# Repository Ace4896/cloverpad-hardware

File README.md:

# Cloverpad - Hardware

**NOTE**: This project is still a work-in-progress, this note will be removed once it's ready!

This repository contains the hardware designs for the Cloverpad, a 3-key keypad for osu! themed after [MORE MORE JUMP!](https://www.sekaipedia.org/wiki/MORE_MORE_JUMP!) from Project Sekai.

... picture of finished keypad ...

There are two PCB variants for this keypad:

- **Cloverpad HE**: PCB for use with hall effect switches (e.g. Wooting Lekker, Gateron KS-20), themed after [Haruka Kiritani](https://www.sekaipedia.org/wiki/Kiritani_Haruka).
- **Cloverpad MX**: PCB for use with regular MX-style mechanical switches, themed after [Minori Hanasato](https://www.sekaipedia.org/wiki/Hanasato_Minori).

## Usage

Make sure you have the following things installed:

- [FreeCAD 0.21](https://www.freecad.org/)
- [KiCad 8](https://www.kicad.org/) with the following plugins:
  - [marbastlib Keyboard Footprints](https://github.com/ebastler/marbastlib)
  - [KiCad JLCPCB Tools](https://github.com/Bouni/kicad-jlcpcb-tools) (if you're using JLC for manufacturing the PCB)

Clone the repository:

```bash
git clone git@github.com:Cloverpad/cloverpad-hardware.git
```

Then navigate to the folder for the revision you're interested in:

- [Rev. 2](./rev2)
- [Rev. 1](./rev1) (Cloverpad MX only; not recommended due to design flaws)

## Additional Files

These project files were used to help design the case and PCB:

- [**assets**](./assets): Miscellaneous assets - logos, character emotes etc.
- [**notes**](./notes): Personal notes for this project - you may find them useful if you're designing a keypad/keyboard of your own
- [**kle**](./kle): Keypad layouts generated by [Keyboard Layout Editor](http://www.keyboard-layout-editor.com/)

## Licensing

This project is licensed under [CERN-OHL-S-2.0](./LICENSE).

Below is a list of assets used from other projects:

- [Project Sekai: Colourful Stage!](https://www.colorfulstage.com/)
  - © SEGA / © Colorful Palette Inc. / © Crypton Future Media, INC.
  - This is a fan project and has no affiliation with SEGA, Colorful Palette, or Crypton Future Media.
  - Assets from MORE MORE JUMP! and its characters are used in the PCB designs.
- [ConstantinoSchillebeeckx/cherry-mx-switch](https://github.com/ConstantinoSchillebeeckx/cherry-mx-switch)
  - [MIT License](https://github.com/ConstantinoSchillebeeckx/cherry-mx-switch/blob/master/LICENSE)
  - The Cherry MX Switch 3D model is used in the minimal PCB.
- [ebastler/marbastlib](https://github.com/ebastler/marbastlib)
  - [CERN-OHL-P-2.0 License](https://github.com/ebastler/marbastlib/blob/main/LICENSE)
  - Various KiCad symbols and footprints are used in the PCB designs and the minimal PCB.

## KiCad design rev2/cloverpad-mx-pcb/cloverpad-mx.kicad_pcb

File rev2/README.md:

# Cloverpad rev. 2

**NOTE**: This revision is still a work-in-progress, this note will be removed once it's ready!

This folder contains the hardware designs for the Cloverpad rev. 2. This is an incremental improvement over rev. 1, which resolves various issues with the 3D printed case.

Features:

- RP2040 MCU
- Cloverpad HE supports hot-swappable MX-style hall effect switches
- Cloverpad MX supports hot-swappable MX-style digital switches
- 3D printed case w/ threaded inserts

Required parts (for reference):

- 3D printed case + PCB
- USB Type-C cable
- 8x M2x6mm screws
- 8x M2x3mm threaded inserts
- Rubber feet

## Design Files

- [`cloverpad-case.FCStd`](./cloverpad-case.FCStd): FreeCAD 0.21 project for the 3D printed case.
- [`cloverpad-he-pcb`](./cloverpad-he-pcb): KiCad 8 project for the Cloverpad HE rev. 2 PCB.
- [`cloverpad-mx-pcb`](./cloverpad-mx-pcb): KiCad 8 project for the Cloverpad MX rev. 2 PCB.

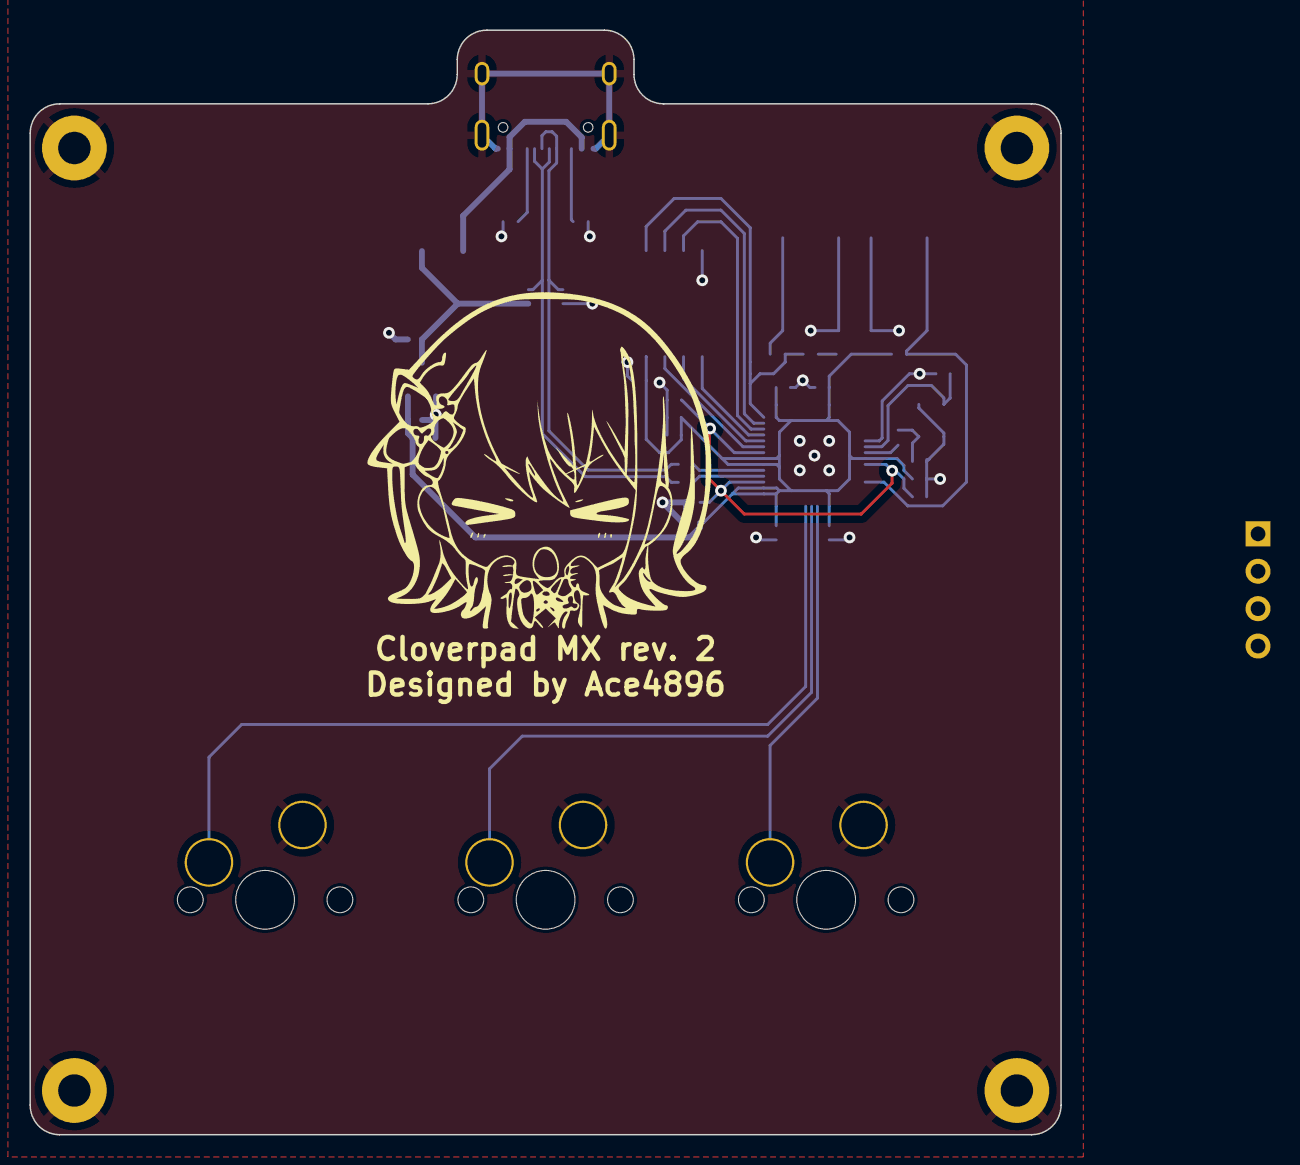
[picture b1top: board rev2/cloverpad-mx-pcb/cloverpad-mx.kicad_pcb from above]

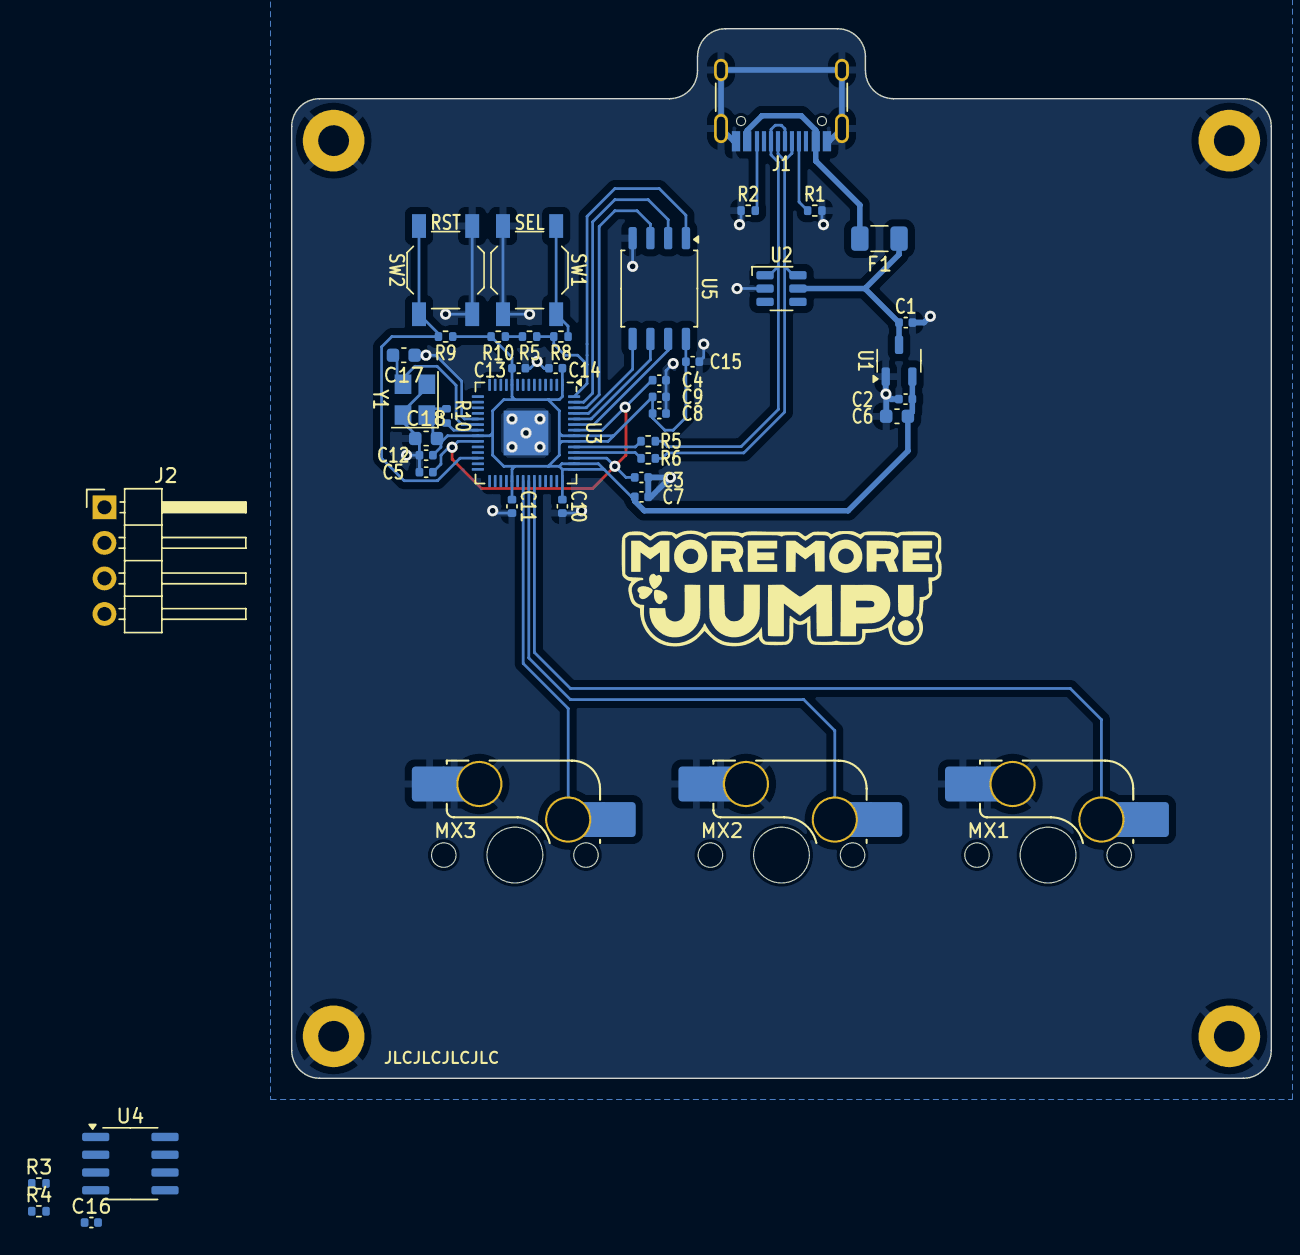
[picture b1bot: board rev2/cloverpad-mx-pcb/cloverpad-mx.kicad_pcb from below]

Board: 2 copper layers, 70.0 x 75.0 mm, 47 parts (43 on the bottom side), 29 nets.

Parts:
C1, C2, C3, C7: 1uF; C_0402_1005Metric
C4, C5, C8, C9, C10, C11, C12, C13, C14, C15, C16: 100nF; C_0402_1005Metric
C6: 10uF; C_0603_1608Metric
C17, C18: 30pF; C_0603_1608Metric
F1: 500mA; Fuse_1206_3216Metric
H1, H2, H3, H4: Mounting Hole; MountingHole_2.2mm_M2_Pad
J1: USB_C_Receptacle_USB2.0; USB_C_Receptacle_HRO_TYPE-C-31-M-12
J2: Conn_01x04; PinHeader_1x04_P2.54mm_Horizontal
MX1, MX2, MX3: MX_SW_HS; SW_MX_HS_CPG151101S11_1u
R1, R2, R3, R4, R10: 5k1; R_0402_1005Metric
R5, R6: 27; R_0402_1005Metric
R5#2: 10k (DNF); R_0402_1005Metric
R8, R9, R10#2: 1k; R_0402_1005Metric
SW1, SW2: SW_Push; SW_SPST_TL3342
U1: XC6206P332MR; SOT-23-3
U2: SRV05-4; SOT-23-6-routable
U3: RP2040; QFN-56-1EP_7x7mm_P0.4mm_EP3.2x3.2mm
U4: AT24C32; SOIC-8_3.9x4.9mm_P1.27mm
U5: W25Q128JVS; SOIC-8_5.23x5.23mm_P1.27mm
Y1: 12MHz; Crystal_SMD_3225-4Pin_3.2x2.5mm

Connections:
+1V1: C3.1, C4.1, C5.1, U3.23 (DVDD), U3.45 (VREG_VOUT), U3.50 (DVDD)
+3V3: C2.1, C6.1, C7.1, C8.1, C9.1, C10.1, C11.1, C12.1, C13.1, C14.1, C15.1, C16.1, J2.1, R3.1, R4.1, R5#2.1, R9.1, R10.1, U1.2 (VO), U3.1 (IOVDD), U3.10 (IOVDD), U3.22 (IOVDD), U3.33 (IOVDD), U3.42 (IOVDD), U3.43 (ADC_AVDD), U3.44 (VREG_IN), U3.48 (USB_VDD), U3.49 (IOVDD), U4.8 (VCC), U5.8 (VCC)
+5V: C1.1, F1.1, U1.3 (VI), U2.5 (VP)
/EEPROM_SCL: R4.2, U3.3 (GPIO1), U4.6 (SCL)
/EEPROM_SDA: R3.2, U3.2 (GPIO0), U4.5 (SDA)
/K1: MX1.1, U3.40 (GPIO28_ADC2)
/K2: MX2.1, U3.39 (GPIO27_ADC1)
/K3: MX3.1, U3.38 (GPIO26_ADC0)
/QSPI_SCLK: U3.52 (QSPI_SCLK), U5.6 (CLK)
/QSPI_SD0: U3.53 (QSPI_SD0), U5.5 (DI(IO0))
/QSPI_SD1: U3.55 (QSPI_SD1), U5.2 (DO(IO1))
/QSPI_SD2: U3.54 (QSPI_SD2), U5.3 (IO2)
/QSPI_SD3: U3.51 (QSPI_SD3), U5.7 (IO3)
/QSPI_SS: R5#2.2, R8.2, U3.56 (QSPI_SS), U5.1 (~CS)
/RUN: R9.2, SW2.2, U3.26 (RUN)
/SWCLK: J2.2, U3.24 (SWCLK)
/SWD: J2.3, U3.25 (SWD)
/USB_D+: J1.A6 (D+), J1.B6 (D+), R5.1, U2.1 (IO1)
/USB_D-: J1.A7 (D-), J1.B7 (D-), R6.1, U2.6 (IO4)
/USB_DM: R6.2, U3.46 (USB_DM)
/USB_DP: R5.2, U3.47 (USB_DP)
/XIN: C17.2, U3.20 (XIN), Y1.3
/XOUT: R10#2.2, U3.21 (XOUT)
GND: C1.2, C2.2, C3.2, C4.2, C5.2, C6.2, C7.2, C8.2, C9.2, C10.2, C11.2, C12.2, C13.2, C14.2, C15.2, C16.2, C17.1, C18.1, H1.1, H2.1, H3.1, H4.1, J1.A1 (GND), J1.A12 (GND), J1.B1 (GND), J1.B12 (GND), J1.S1 (SHIELD), J2.4, MX1.2, MX2.2, MX3.2, R1.2, R2.2, SW1.1, SW2.1, U1.1 (GND), U2.2 (VN), U3.19 (TESTEN), U3.57 (GND), U4.1 (A0), U4.2 (A1), U4.3 (A2), U4.4 (GND), U4.7 (WP), U5.4 (GND), Y1.2, Y1.4
unnamed: C18.2, R10#2.1, Y1.1
unnamed: F1.2, J1.A4 (VBUS), J1.A9 (VBUS), J1.B4 (VBUS), J1.B9 (VBUS)
unnamed: J1.A5 (CC1), R1.1
unnamed: J1.B5 (CC2), R2.1
unnamed: R8.1, SW1.2

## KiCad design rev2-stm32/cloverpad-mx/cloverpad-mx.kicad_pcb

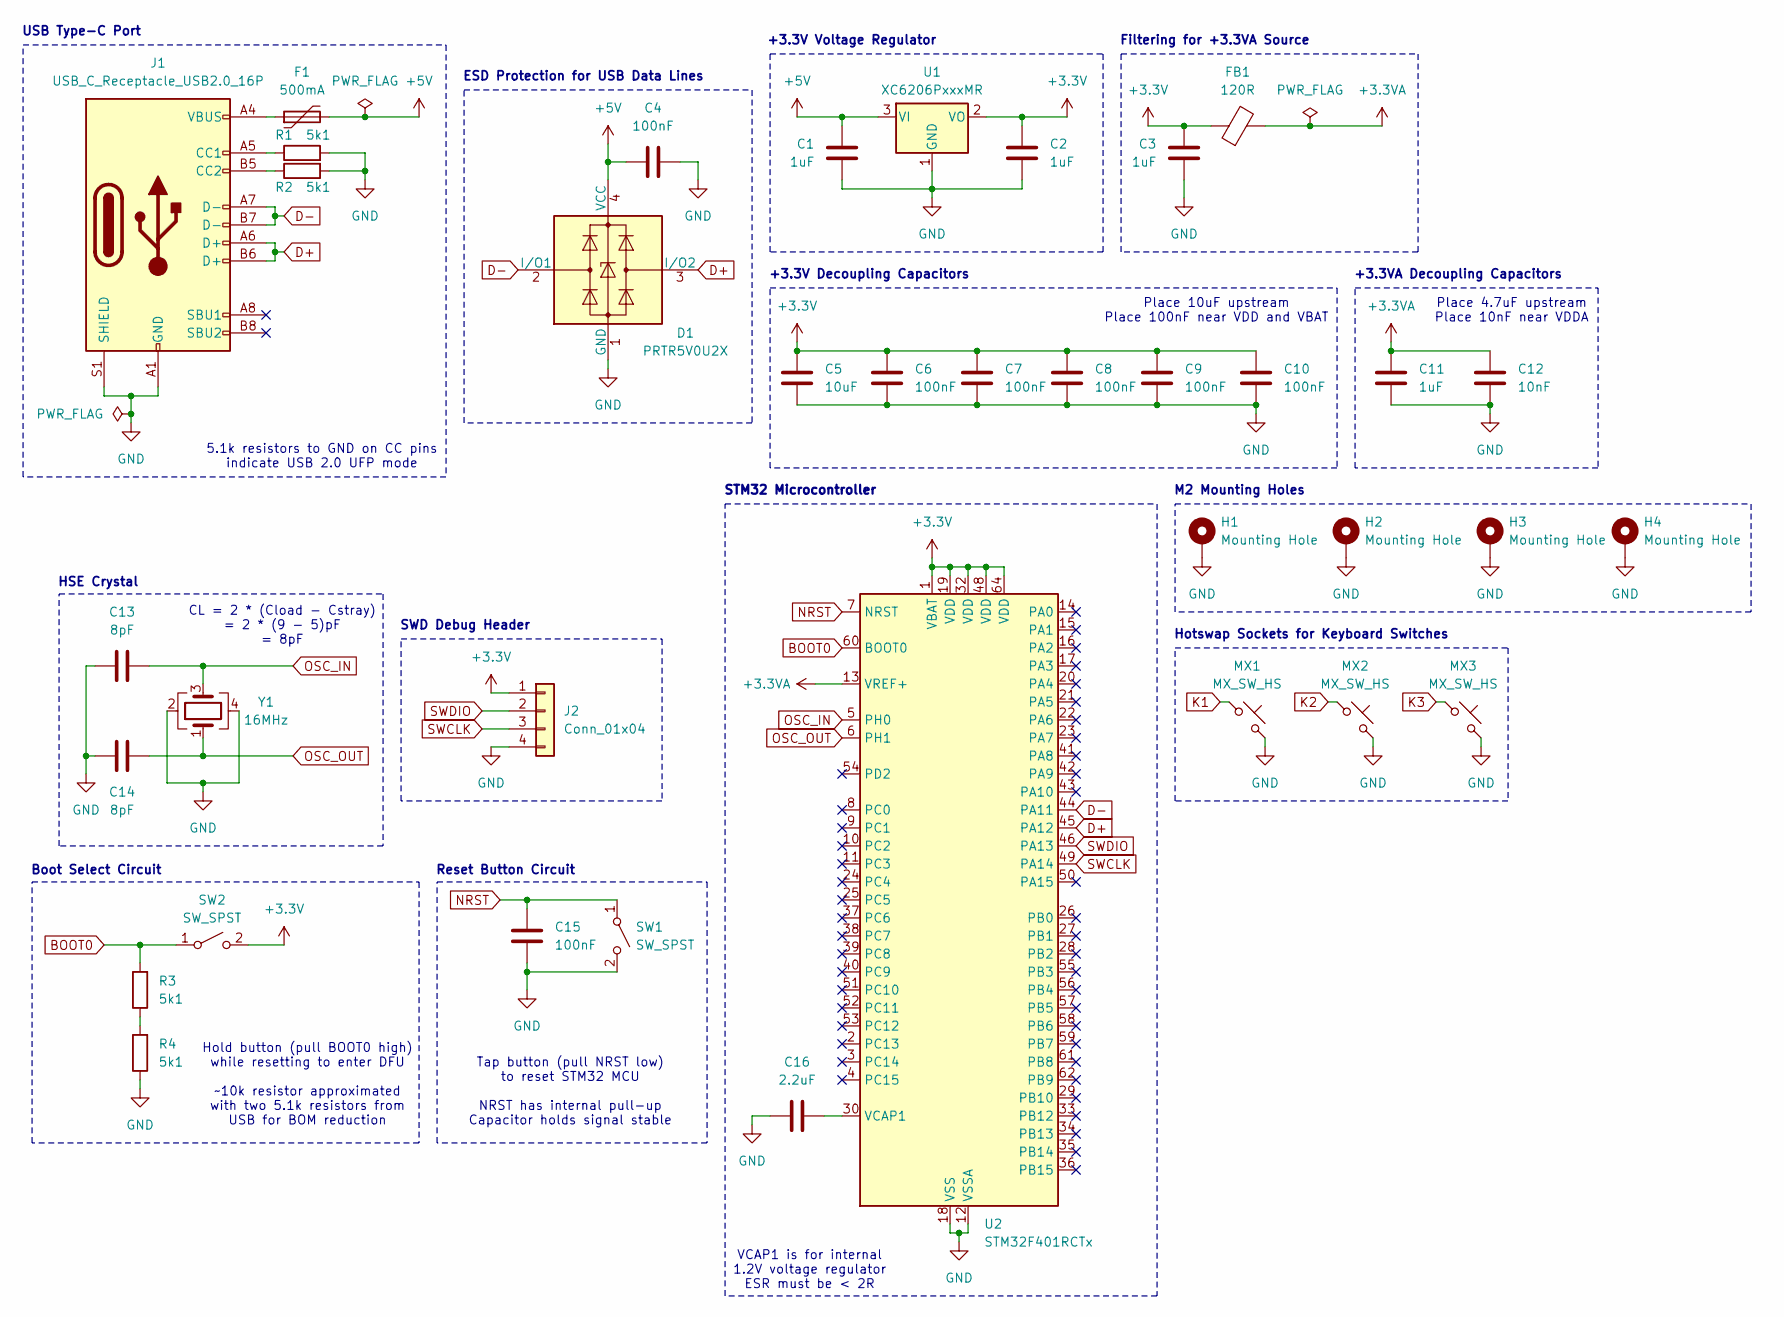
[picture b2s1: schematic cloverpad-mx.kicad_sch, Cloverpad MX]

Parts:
C1, C2, C3, C11: 1uF; C_0402_1005Metric; LCSC C52923
C4, C6, C7, C8, C9, C10, C15: 100nF; C_0402_1005Metric; LCSC C1525
C5: 10uF; C_0603_1608Metric; LCSC C19702
C12: 10nF; C_0402_1005Metric; LCSC C15195
C13, C14: 8pF; C_0402_1005Metric; LCSC C296006
C16: 2.2uF; C_0603_1608Metric; LCSC C23630
D1: PRTR5V0U2X; SOT-143; LCSC C2827688
F1: 500mA; Fuse_0805_2012Metric; LCSC C269106
FB1: 120R; L_0402_1005Metric; LCSC C141722
H1, H2, H3, H4: Mounting Hole; MountingHole_2.2mm_M2_Pad
J1: USB_C_Receptacle_USB2.0_16P; USB_C_Receptacle_HRO_TYPE-C-31-M-12; LCSC C165948
J2: Conn_01x04; PinHeader_1x04_P2.54mm_Horizontal; LCSC C91552
MX1, MX2, MX3: MX_SW_HS; SW_MX_HS_CPG151101S11_1u; LCSC C5156480
R1, R2, R3, R4: 5k1; R_0402_1005Metric; LCSC C25905
SW1, SW2: SW_SPST; SW_SPST_TL3342; LCSC C318884
U1: XC6206PxxxMR; SOT-23-3; LCSC C5446
U2: STM32F401RCTx; LQFP-64_10x10mm_P0.5mm; LCSC C74524
Y1: 16MHz; Crystal_SMD_3225-4Pin_3.2x2.5mm; LCSC C13738

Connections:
+3.3V: C2.1, C3.1, C5.1, C6.1, C7.1, C8.1, C9.1, C10.1, FB1.1, J2.1, SW2.2 (B), U1.2 (VO), U2.1 (VBAT), U2.19 (VDD), U2.32 (VDD), U2.48 (VDD), U2.64 (VDD)
+3.3VA: C11.1, C12.1, FB1.2, U2.13 (VREF+)
+5V: C1.1, C4.1, D1.4 (VCC), F1.2, U1.3 (VI)
BOOT0: R3.2, SW2.1 (A), U2.60 (BOOT0)
D+: D1.3 (I/O2), J1.A6 (D+), J1.B6 (D+), U2.45 (PA12)
D-: D1.2 (I/O1), J1.A7 (D-), J1.B7 (D-), U2.44 (PA11)
GND: C1.2, C2.2, C3.2, C4.2, C5.2, C6.2, C7.2, C8.2, C9.2, C10.2, C11.2, C12.2, C13.1, C14.2, C15.2, C16.2, D1.1 (GND), H1.1, H2.1, H3.1, H4.1, J1.A1 (GND), J1.A12 (GND), J1.B1 (GND), J1.B12 (GND), J1.S1 (SHIELD), J2.4, MX1.2, MX2.2, MX3.2, R1.2, R2.2, R4.1, SW1.2 (B), U1.1 (GND), U2.12 (VSSA), U2.18 (VSS), U2.31 (VSS), U2.47 (VSS), U2.63 (VSS), Y1.2, Y1.4
K1: MX1.1
K2: MX2.1
K3: MX3.1
NRST: C15.1, SW1.1 (A), U2.7 (NRST)
unnamed: F1.1, J1.A4 (VBUS), J1.A9 (VBUS), J1.B4 (VBUS), J1.B9 (VBUS)
unnamed: J1.A5 (CC1), R1.1
unnamed: J1.B5 (CC2), R2.1
unnamed: R3.1, R4.2
unnamed: C16.1, U2.30 (VCAP1)
OSC_IN: C13.2, U2.5 (PH0), Y1.3
OSC_OUT: C14.1, U2.6 (PH1), Y1.1
SWCLK: J2.3, U2.49 (PA14)
SWDIO: J2.2, U2.46 (PA13)

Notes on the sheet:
VCAP1 is for internal 1.2V voltage regulator ESR must be < 2R
HSE Crystal
M2 Mounting Holes
Place 10uF upstream Place 100nF near VDD and VBAT
+3.3V Decoupling Capacitors
Filtering for +3.3VA Source
5.1k resistors to GND on CC pins indicate USB 2.0 UFP mode
ESD Protection for USB Data Lines
USB Type-C Port
+3.3VA Decoupling Capacitors
Hotswap Sockets for Keyboard Switches
Tap button (pull NRST low) to reset STM32 MCU NRST has internal pull-up Capacitor holds signal stable
Boot Select Circuit
Reset Button Circuit
Hold button (pull BOOT0 high) while resetting to enter DFU ~10k resistor approximated with two 5.1k resistors from USB for BOM reduction
SWD Debug Header
STM32 Microcontroller
CL = 2 * (Cload - Cstray) = 2 * (9 - 5)pF = 8pF
Place 4.7uF upstream Place 10nF near VDDA
+3.3V Voltage Regulator

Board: 2 copper layers, 37 parts (37 on the bottom side), 17 nets, no tracks yet.

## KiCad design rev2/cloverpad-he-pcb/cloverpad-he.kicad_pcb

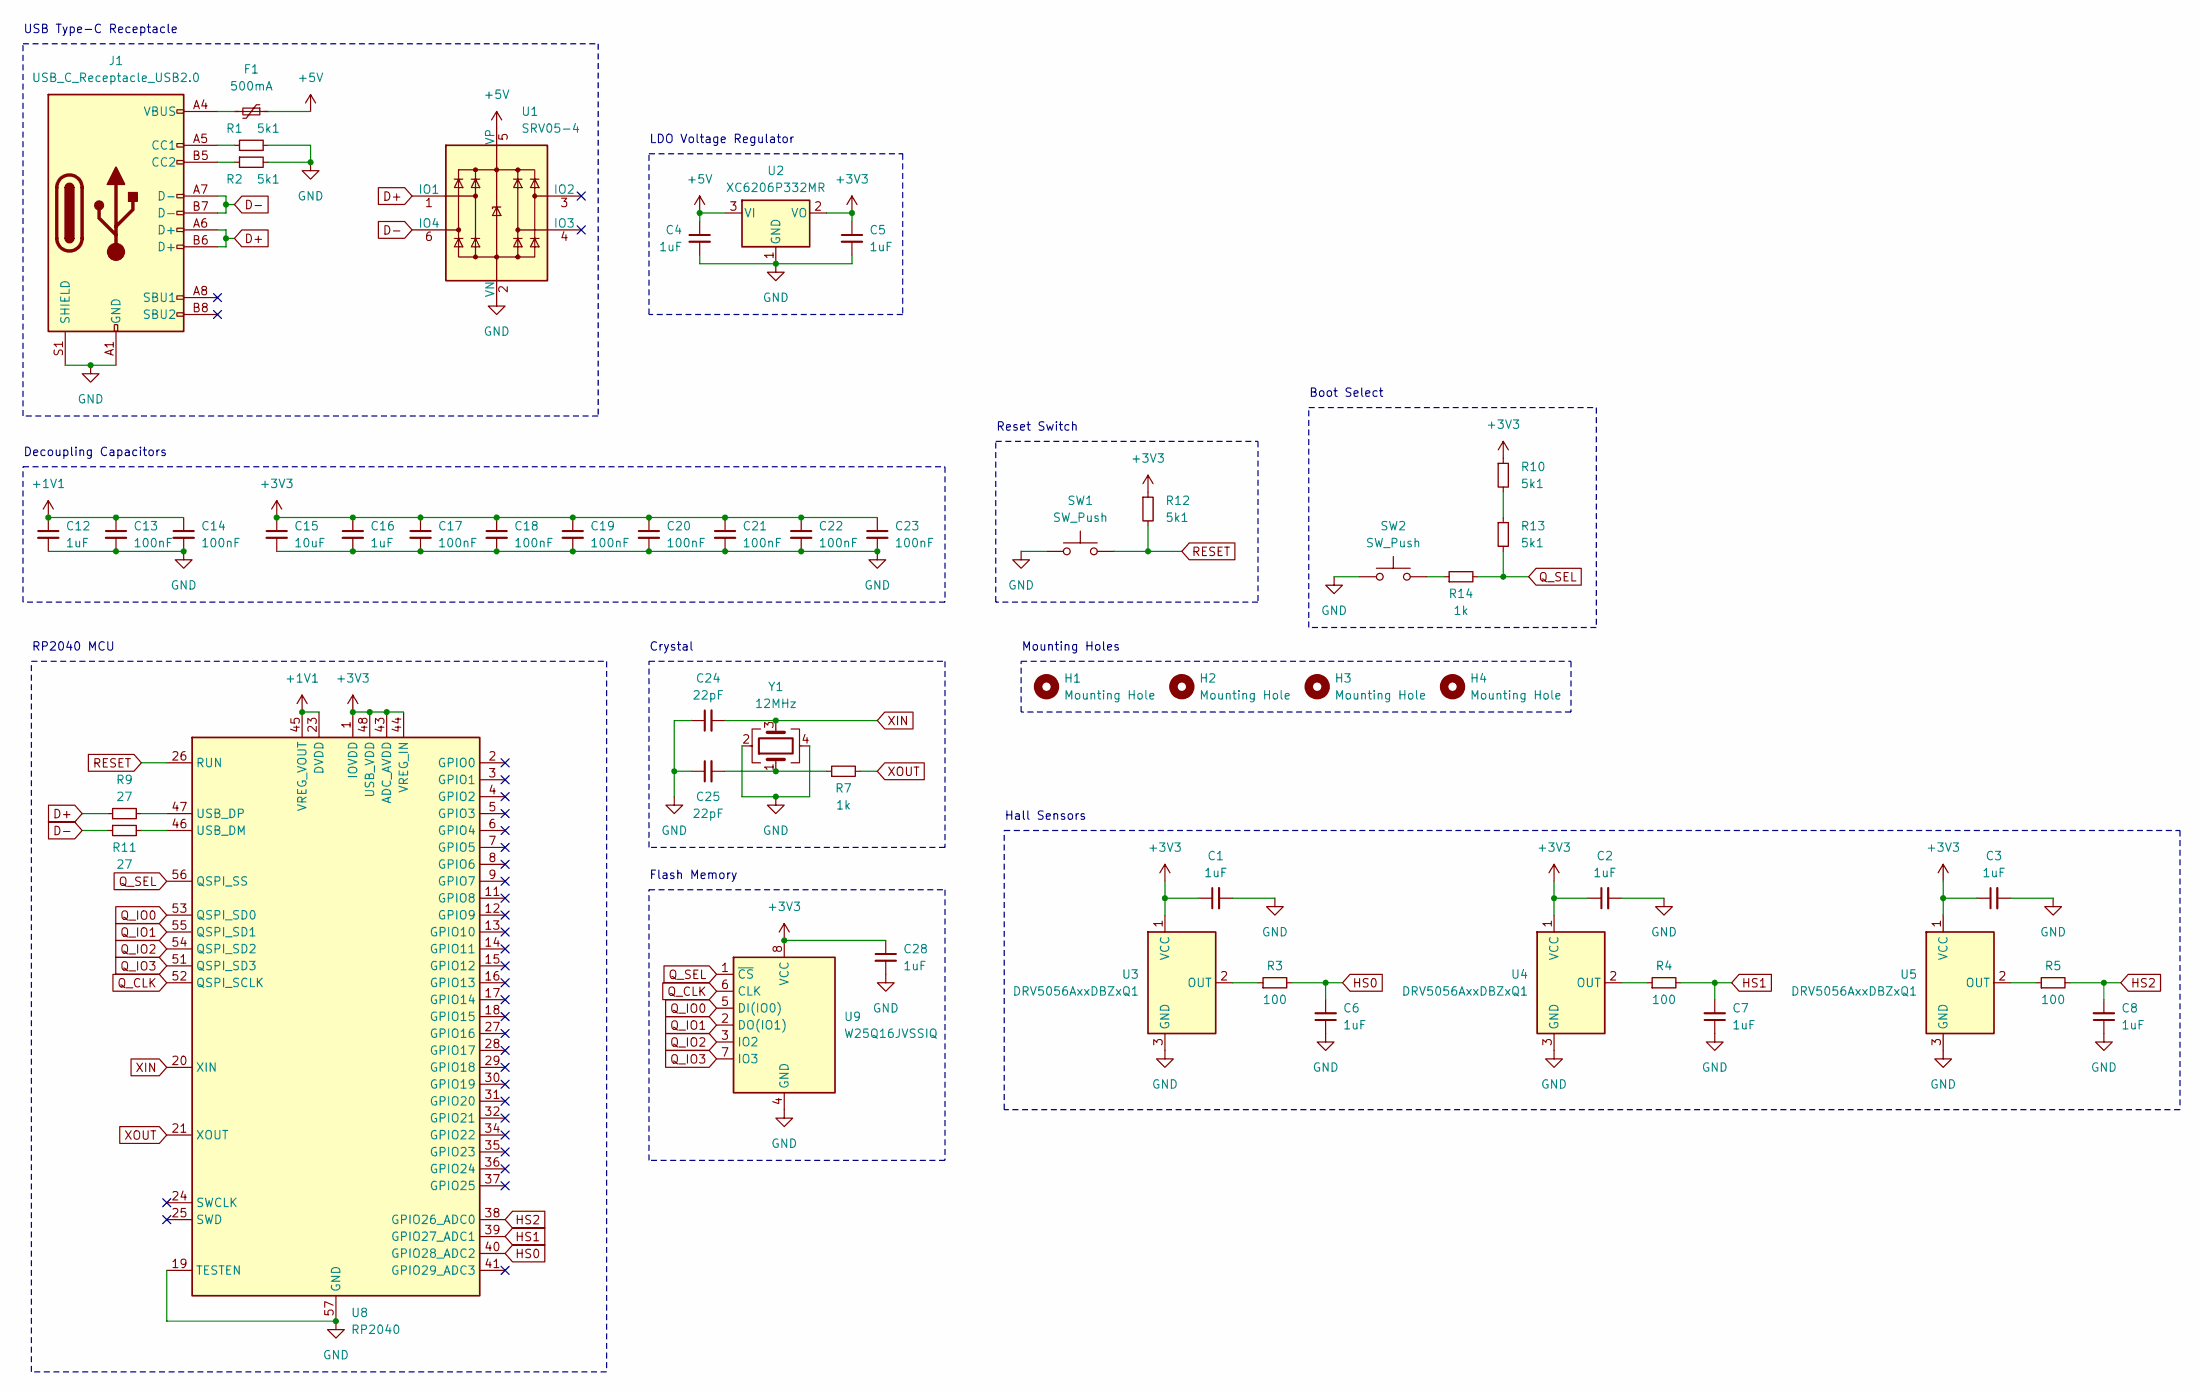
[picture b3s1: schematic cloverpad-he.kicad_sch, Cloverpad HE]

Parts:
C1, C2, C3, C4, C5, C6, C7, C8, C12, C16, C28: 1uF; C_0402_1005Metric; LCSC C52923
C13, C14, C17, C18, C19, C20, C21, C22, C23: 100nF; C_0402_1005Metric; LCSC C1525
C15: 10uF; C_0603_1608Metric; LCSC C19702
C24, C25: 22pF; C_0402_1005Metric; LCSC C1555
F1: 500mA; Fuse_1206_3216Metric; LCSC C170165
H1, H2, H3, H4: Mounting Hole; MountingHole_2.2mm_M2
J1: USB_C_Receptacle_USB2.0; USB_C_Receptacle_HRO_TYPE-C-31-M-12; LCSC C165948
R1, R2, R10, R12, R13: 5k1; R_0402_1005Metric; LCSC C25905
R3, R4, R5: 100; R_0402_1005Metric; LCSC C25076
R7, R14: 1k; R_0402_1005Metric; LCSC C11702
R9, R11: 27; R_0402_1005Metric; LCSC C25100
SW1, SW2: SW_Push; SW_SPST_TL3342; LCSC C318884
U1: SRV05-4; SOT-23-6-routable; LCSC C2836319
U2: XC6206P332MR; SOT-23-3; LCSC C5446
U3, U4, U5: DRV5056AxxDBZxQ1; KS-20-1U-DRV5056; LCSC C2152965
U8: RP2040; QFN-56-1EP_7x7mm_P0.4mm_EP3.2x3.2mm; LCSC C2040
U9: W25Q16JVSSIQ; SOIC-8_5.23x5.23mm_P1.27mm; LCSC C131025
Y1: 12MHz; Crystal_SMD_3225-4Pin_3.2x2.5mm; LCSC C9002

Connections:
+1V1: C12.1, C13.1, C14.1, U8.23 (DVDD), U8.45 (VREG_VOUT), U8.50 (DVDD)
+3V3: C1.1, C2.1, C3.1, C5.1, C15.1, C16.1, C17.1, C18.1, C19.1, C20.1, C21.1, C22.1, C23.1, C28.1, R10.1, R12.1, U2.2 (VO), U3.1 (VCC), U4.1 (VCC), U5.1 (VCC), U8.1 (IOVDD), U8.10 (IOVDD), U8.22 (IOVDD), U8.33 (IOVDD), U8.42 (IOVDD), U8.43 (ADC_AVDD), U8.44 (VREG_IN), U8.48 (USB_VDD), U8.49 (IOVDD), U9.8 (VCC)
+5V: C4.1, F1.1, U1.5 (VP), U2.3 (VI)
D+: J1.A6 (D+), J1.B6 (D+), R9.1, U1.1 (IO1)
D-: J1.A7 (D-), J1.B7 (D-), R11.1, U1.6 (IO4)
GND: C1.2, C2.2, C3.2, C4.2, C5.2, C6.1, C7.1, C8.1, C12.2, C13.2, C14.2, C15.2, C16.2, C17.2, C18.2, C19.2, C20.2, C21.2, C22.2, C23.2, C24.1, C25.1, C28.2, J1.A1 (GND), J1.A12 (GND), J1.B1 (GND), J1.B12 (GND), J1.S1 (SHIELD), R1.2, R2.2, SW1.1, SW2.1, U1.2 (VN), U2.1 (GND), U3.3 (GND), U4.3 (GND), U5.3 (GND), U8.19 (TESTEN), U8.57 (GND), U9.4 (GND), Y1.2, Y1.4
HS0: C6.2, R3.2, U8.40 (GPIO28_ADC2)
HS1: C7.2, R4.2, U8.39 (GPIO27_ADC1)
HS2: C8.2, R5.2, U8.38 (GPIO26_ADC0)
unnamed: C25.2, R7.1, Y1.1
unnamed: F1.2, J1.A4 (VBUS), J1.A9 (VBUS), J1.B4 (VBUS), J1.B9 (VBUS)
unnamed: J1.A5 (CC1), R1.1
unnamed: J1.B5 (CC2), R2.1
unnamed: R10.2, R13.1
unnamed: R14.1, SW2.2
unnamed: R3.1, U3.2 (OUT)
unnamed: R4.1, U4.2 (OUT)
unnamed: R5.1, U5.2 (OUT)
unnamed: R11.2, U8.46 (USB_DM)
unnamed: R9.2, U8.47 (USB_DP)
Q_CLK: U8.52 (QSPI_SCLK), U9.6 (CLK)
Q_IO0: U8.53 (QSPI_SD0), U9.5 (DI(IO0))
Q_IO1: U8.55 (QSPI_SD1), U9.2 (DO(IO1))
Q_IO2: U8.54 (QSPI_SD2), U9.3 (IO2)
Q_IO3: U8.51 (QSPI_SD3), U9.7 (IO3)
Q_SEL: R13.2, R14.2, U8.56 (QSPI_SS), U9.1 (~CS)
RESET: R12.2, SW1.2, U8.26 (RUN)
XIN: C24.2, U8.20 (XIN), Y1.3
XOUT: R7.2, U8.21 (XOUT)

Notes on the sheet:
Reset Switch
USB Type-C Receptacle
Mounting Holes
Decoupling Capacitors
LDO Voltage Regulator
Hall Sensors
RP2040 MCU
Flash Memory
Boot Select
Crystal

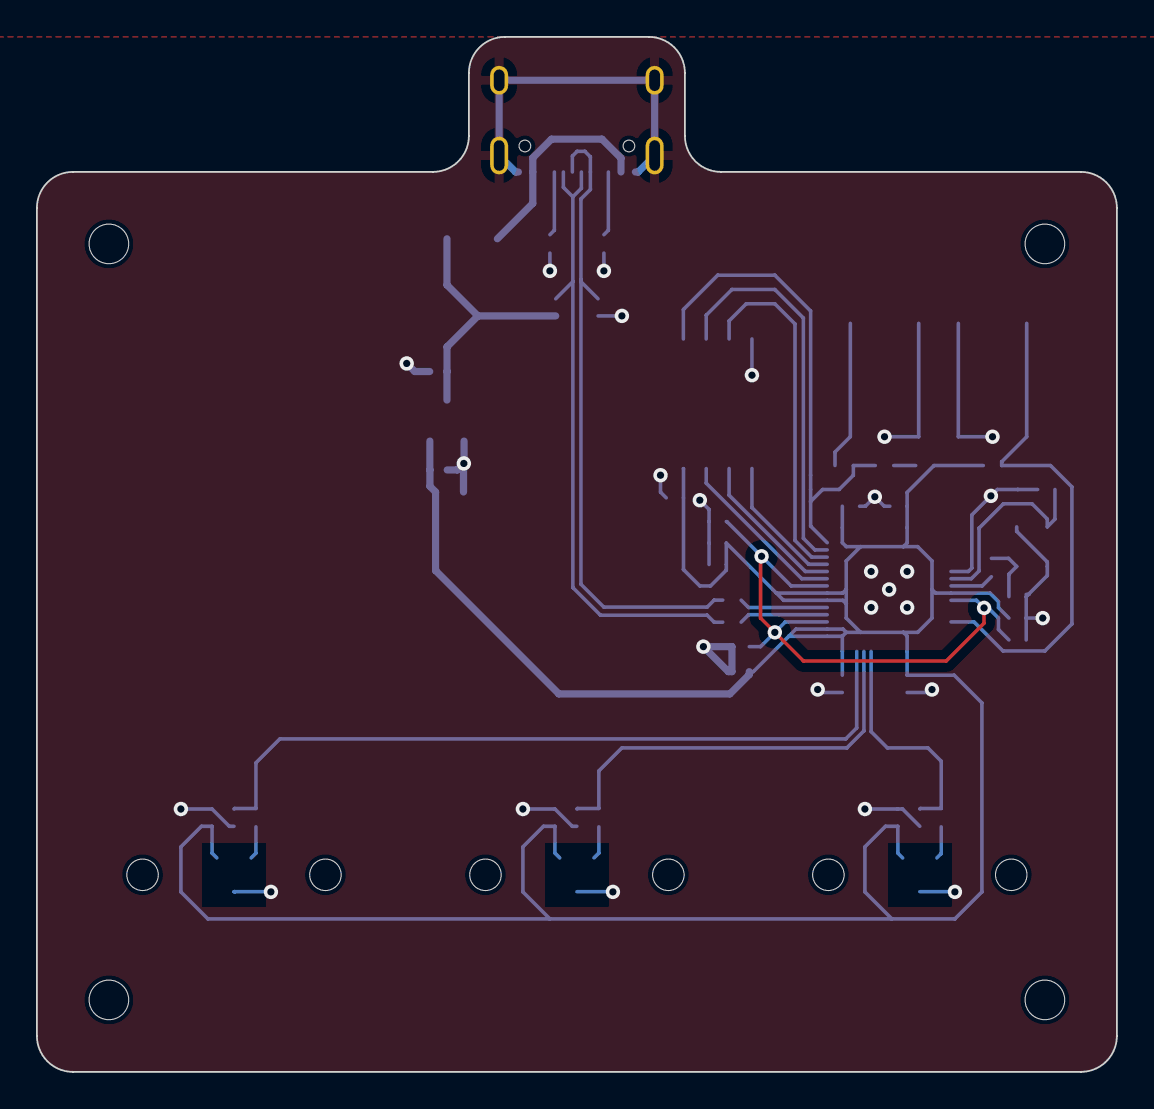
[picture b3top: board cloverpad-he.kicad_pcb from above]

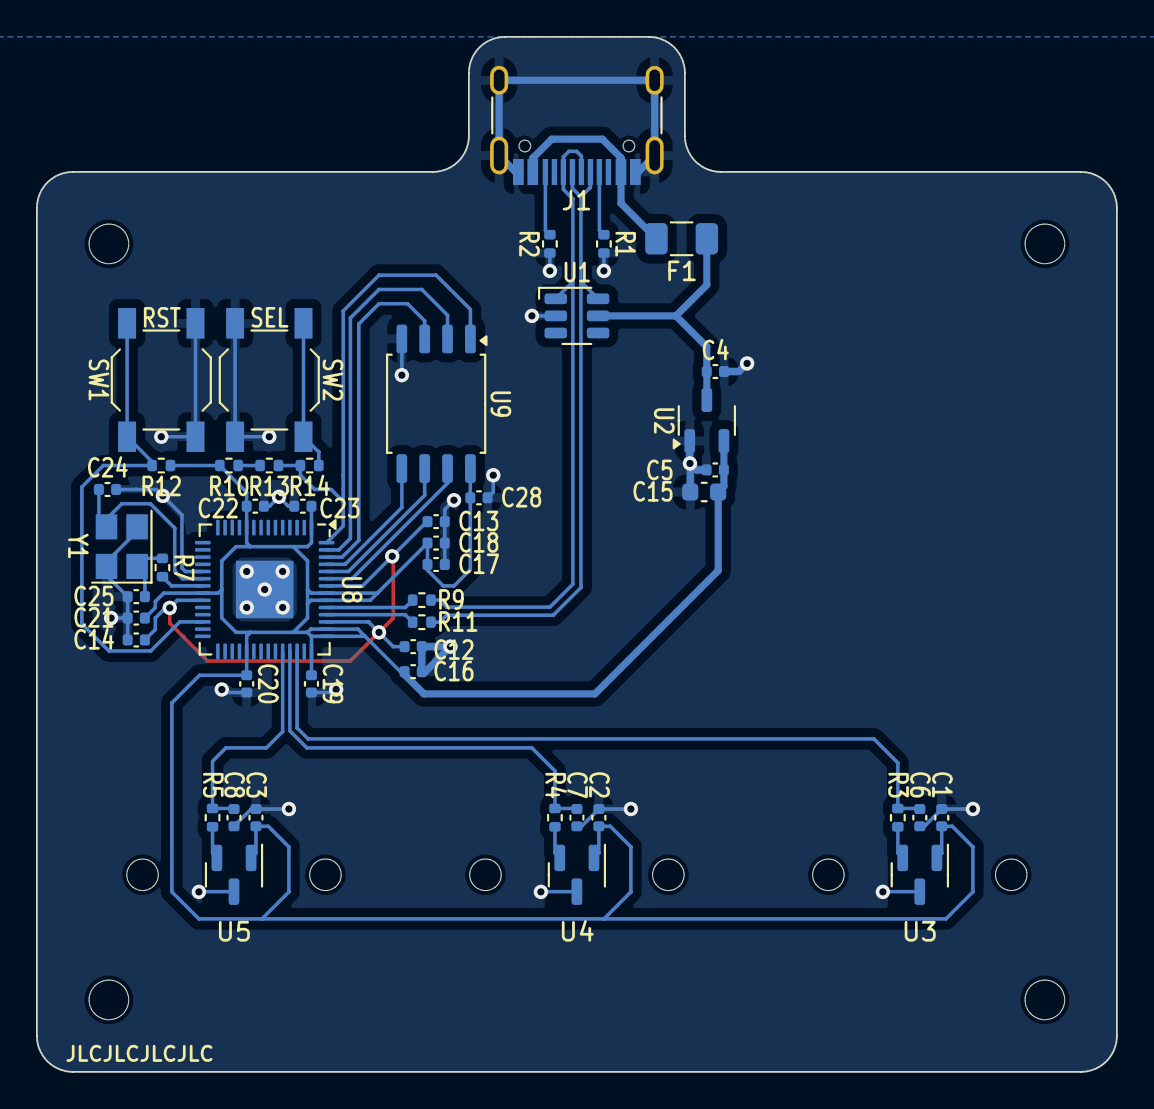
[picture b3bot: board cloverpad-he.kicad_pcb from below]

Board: 2 copper layers, 60.0 x 57.5 mm, 51 parts (47 on the bottom side), 29 nets.

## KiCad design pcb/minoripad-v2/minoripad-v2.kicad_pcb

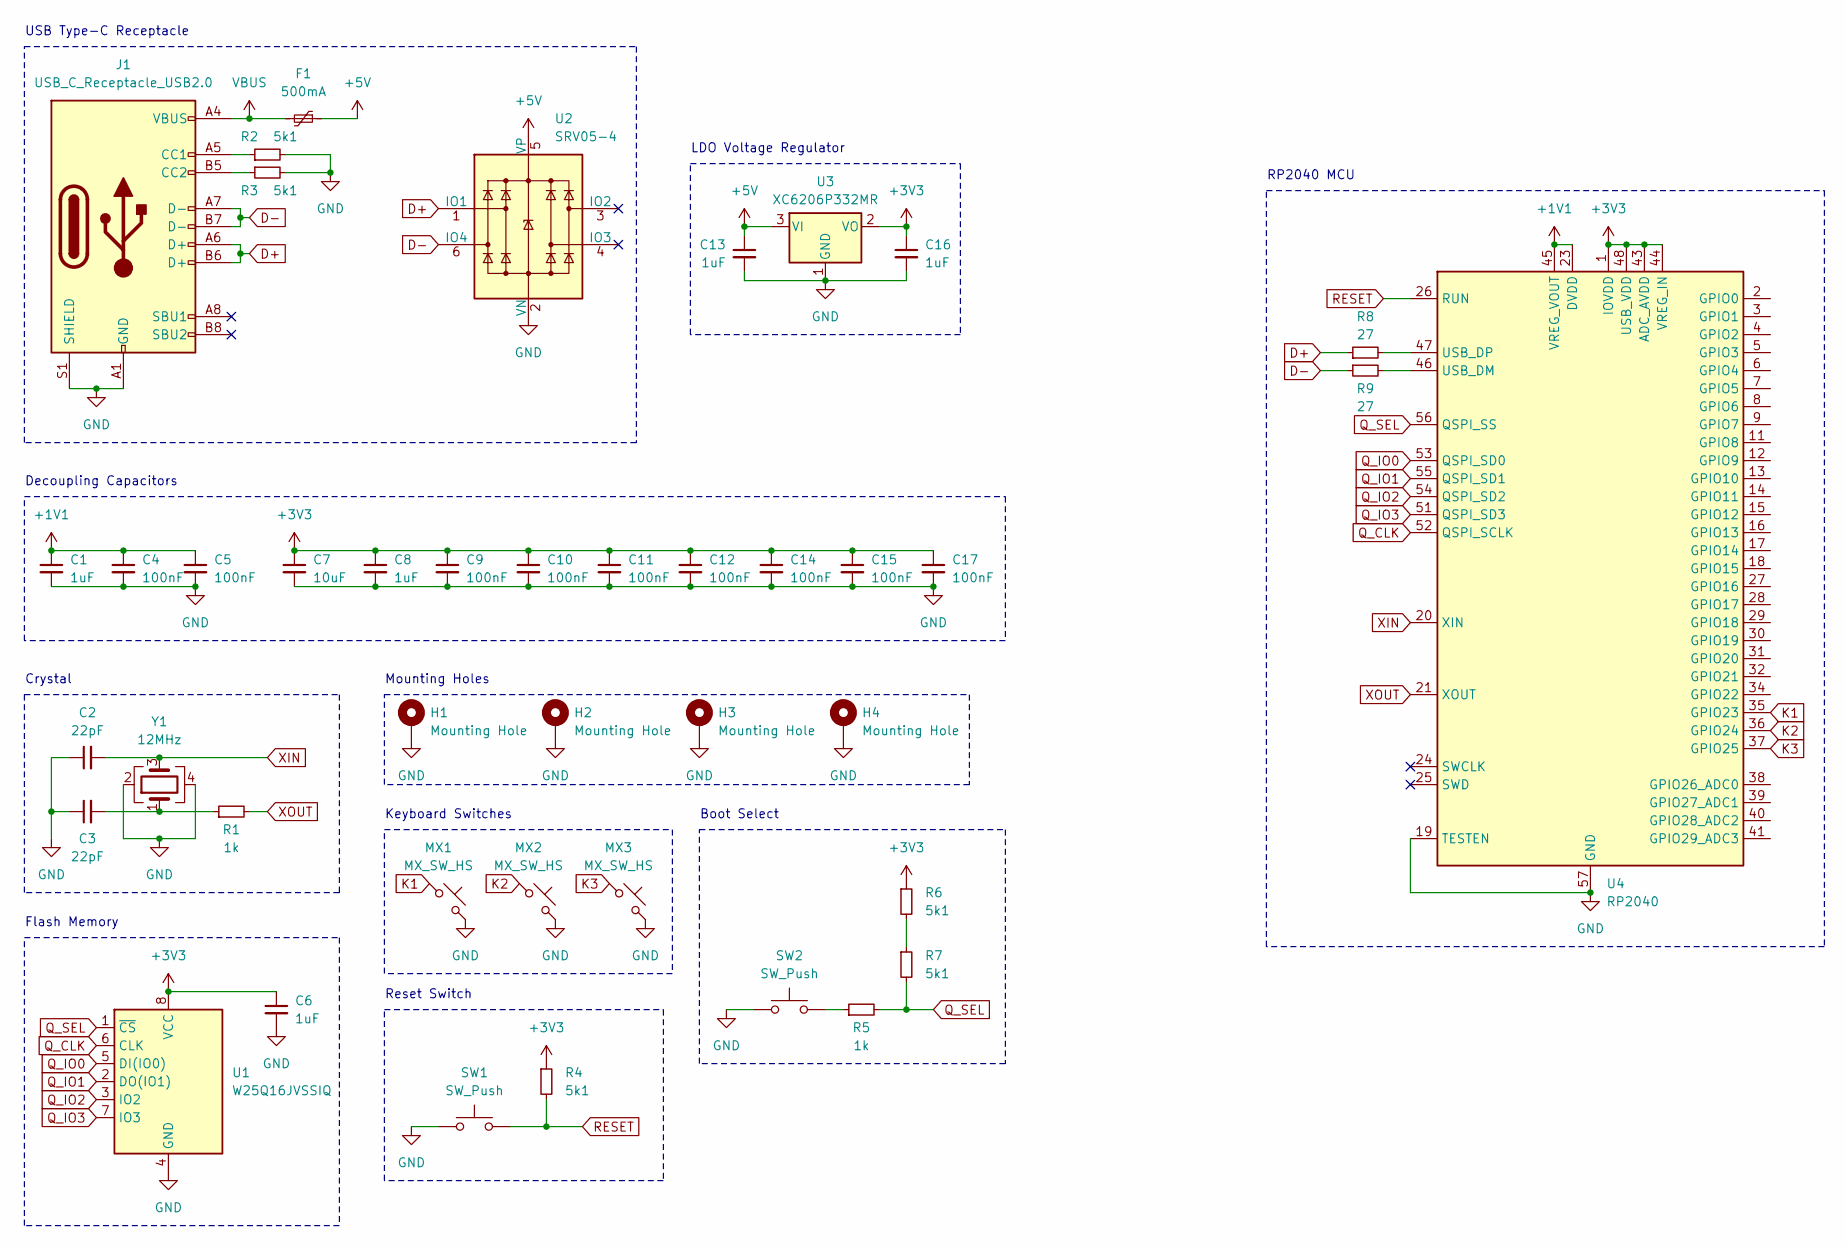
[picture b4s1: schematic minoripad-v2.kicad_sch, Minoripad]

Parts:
C1, C6, C8, C13, C16: 1uF; C_0402_1005Metric; LCSC C52923
C2, C3: 22pF; C_0402_1005Metric; LCSC C1555
C4, C5, C9, C10, C11, C12, C14, C15, C17: 100nF; C_0402_1005Metric; LCSC C1525
C7: 10uF; C_0603_1608Metric; LCSC C19702
F1: 500mA; Fuse_1206_3216Metric; LCSC C170165
H1, H2, H3, H4: Mounting Hole; MountingHole_3.5mm_Pad
J1: USB_C_Receptacle_USB2.0; USB_C_Receptacle_HRO_TYPE-C-31-M-12; LCSC C165948
MX1, MX2, MX3: MX_SW_HS; SW_MX_HS_1u; LCSC C5156480
R1, R5: 1k; R_0402_1005Metric; LCSC C11702
R2, R3, R4, R6, R7: 5k1; R_0402_1005Metric; LCSC C25905
R8, R9: 27; R_0402_1005Metric; LCSC C25100
SW1, SW2: SW_Push; SW_SPST_TL3342; LCSC C318884
U1: W25Q16JVSSIQ; SOIC-8_5.23x5.23mm_P1.27mm; LCSC C131025
U2: SRV05-4; SOT-23-6-routable; LCSC C2836319
U3: XC6206P332MR; SOT-23-3; LCSC C5446
U4: RP2040; QFN-56-1EP_7x7mm_P0.4mm_EP3.2x3.2mm; LCSC C2040
Y1: 12MHz; Crystal_SMD_3225-4Pin_3.2x2.5mm; LCSC C9002

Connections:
+1V1: C1.1, C4.1, C5.1, U4.23 (DVDD), U4.45 (VREG_VOUT), U4.50 (DVDD)
+3V3: C6.1, C7.1, C8.1, C9.1, C10.1, C11.1, C12.1, C14.1, C15.1, C16.1, C17.1, R4.1, R6.1, U1.8 (VCC), U3.2 (VO), U4.1 (IOVDD), U4.10 (IOVDD), U4.22 (IOVDD), U4.33 (IOVDD), U4.42 (IOVDD), U4.43 (ADC_AVDD), U4.44 (VREG_IN), U4.48 (USB_VDD), U4.49 (IOVDD)
+5V: C13.1, F1.1, U2.5 (VP), U3.3 (VI)
D+: J1.A6 (D+), J1.B6 (D+), R8.1, U2.1 (IO1)
D-: J1.A7 (D-), J1.B7 (D-), R9.1, U2.6 (IO4)
GND: C1.2, C2.1, C3.1, C4.2, C5.2, C6.2, C7.2, C8.2, C9.2, C10.2, C11.2, C12.2, C13.2, C14.2, C15.2, C16.2, C17.2, H1.1, H2.1, H3.1, H4.1, J1.A1 (GND), J1.A12 (GND), J1.B1 (GND), J1.B12 (GND), J1.S1 (SHIELD), MX1.2, MX2.2, MX3.2, R2.2, R3.2, SW1.1, SW2.1, U1.4 (GND), U2.2 (VN), U3.1 (GND), U4.19 (TESTEN), U4.57 (GND), Y1.2, Y1.4
K1: MX1.1, U4.35 (GPIO23)
K2: MX2.1, U4.36 (GPIO24)
K3: MX3.1, U4.37 (GPIO25)
unnamed: C3.2, R1.1, Y1.1
unnamed: J1.A5 (CC1), R2.1
unnamed: J1.B5 (CC2), R3.1
unnamed: R5.1, SW2.2
unnamed: R6.2, R7.1
unnamed: R9.2, U4.46 (USB_DM)
unnamed: R8.2, U4.47 (USB_DP)
Q_CLK: U1.6 (CLK), U4.52 (QSPI_SCLK)
Q_IO0: U1.5 (DI(IO0)), U4.53 (QSPI_SD0)
Q_IO1: U1.2 (DO(IO1)), U4.55 (QSPI_SD1)
Q_IO2: U1.3 (IO2), U4.54 (QSPI_SD2)
Q_IO3: U1.7 (IO3), U4.51 (QSPI_SD3)
Q_SEL: R5.2, R7.2, U1.1 (~CS), U4.56 (QSPI_SS)
RESET: R4.2, SW1.2, U4.26 (RUN)
VBUS: F1.2, J1.A4 (VBUS), J1.A9 (VBUS), J1.B4 (VBUS), J1.B9 (VBUS)
XIN: C2.2, U4.20 (XIN), Y1.3
XOUT: R1.2, U4.21 (XOUT)

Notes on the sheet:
USB Type-C Receptacle
Decoupling Capacitors
Mounting Holes
Reset Switch
Boot Select
Keyboard Switches
Flash Memory
LDO Voltage Regulator
Crystal
RP2040 MCU
